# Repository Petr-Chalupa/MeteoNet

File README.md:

# MeteoNet

Simple meteorological net with single root node and multiple sensor nodes.  
Focusing on low power consumption, low data TX and near/far communication.

### FW
> Written in C++  
> No runtime memalloc strategy  
> No unnecessary C++ features

### HW
> Developed in KiCAD  
> Simple design  
> One HW, multiple roles strategy

_For more thorough documentation, please see [docs](/docs)._

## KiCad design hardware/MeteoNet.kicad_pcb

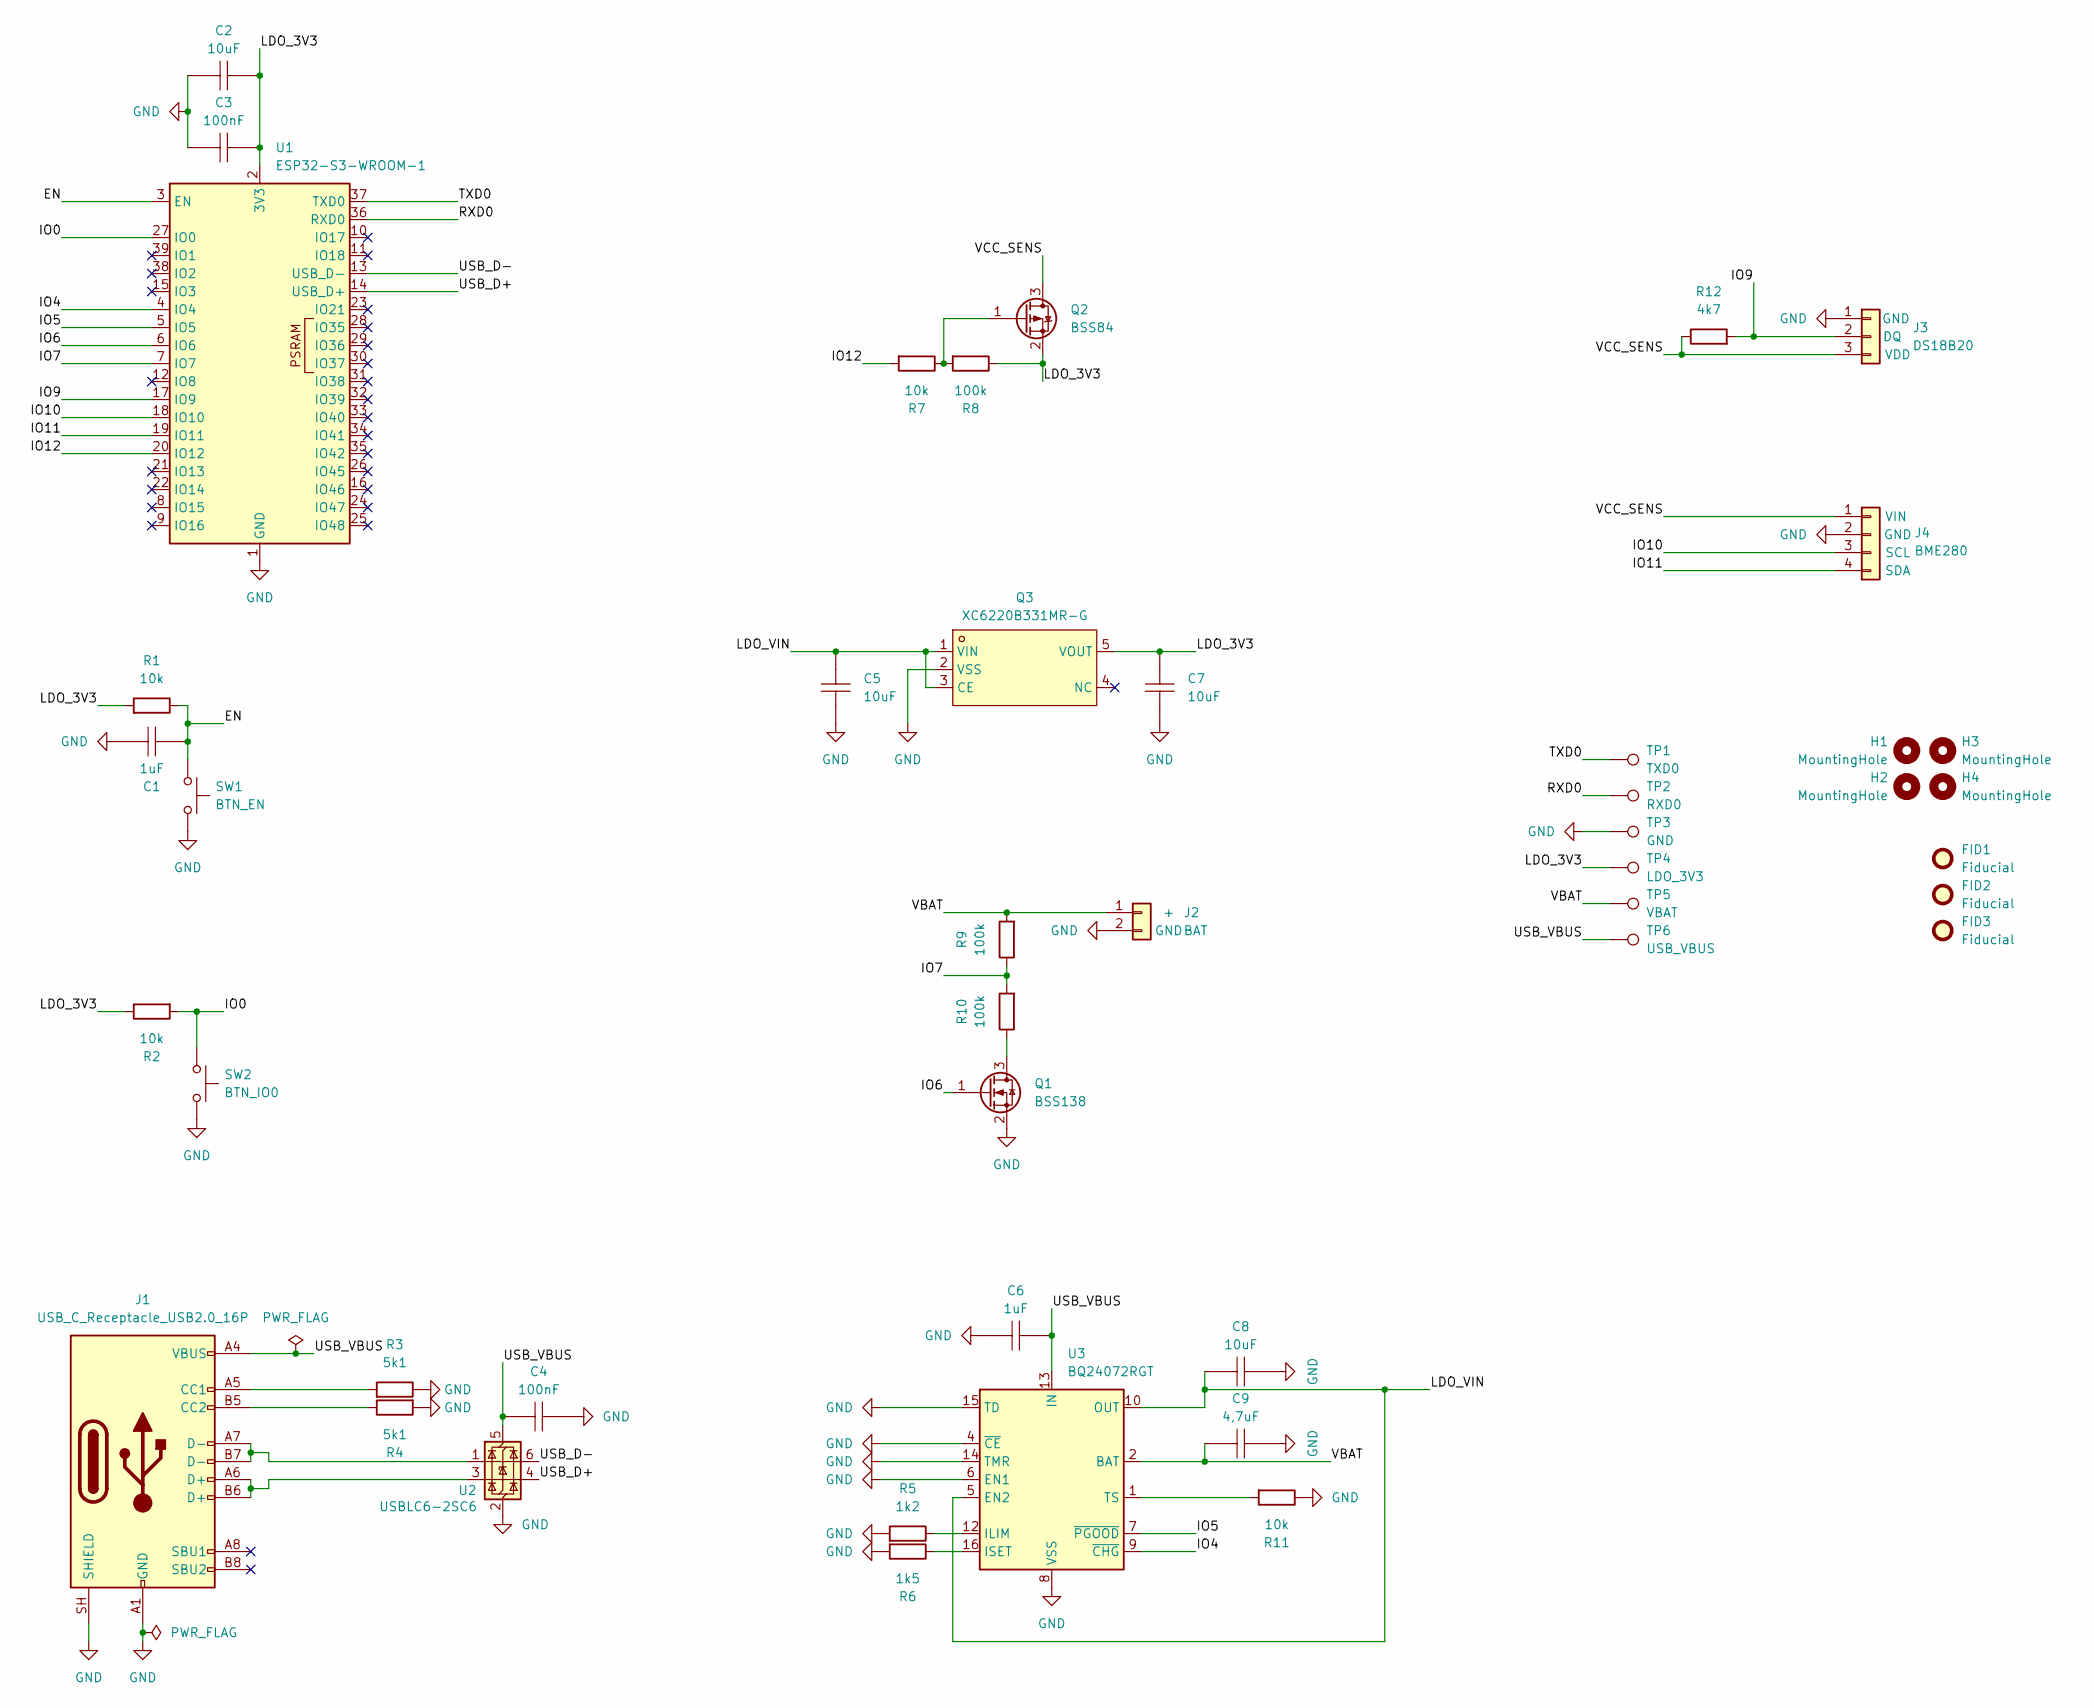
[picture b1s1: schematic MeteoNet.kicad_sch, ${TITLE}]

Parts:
C1: 1uF; C_0603_1608Metric; Voltage Rated 10V; Tolerance ±10%; LCSC Part C19702
C2, C5, C7: 10uF; C_0805_2012Metric; Voltage Rated 10V; Tolerance ±10%; LCSC Part C19702
C3, C4: 100nF; C_0603_1608Metric; Voltage Rated 16V; Tolerance ±10%; LCSC Part C1525
C6: 1uF; C_0603_1608Metric; Voltage Rated 16V; Tolerance ±10%; LCSC Part C1525
C8: 10uF; C_0805_2012Metric; Voltage Rated 16V; Tolerance ±10%; LCSC Part C1525
C9: 4,7uF; C_0805_2012Metric; Voltage Rated 16V; Tolerance ±10%; LCSC Part C1525
FID1, FID2, FID3: Fiducial; Fiducial_1mm_Mask2mm
H1, H2, H3, H4: MountingHole; MountingHole_2.5mm_Pad
J1: USB_C_Receptacle_USB2.0_16P; USB_C_Receptacle_HRO_TYPE-C-31-M-12; LCSC Part # C165948
J2: BAT; JST_PH_B2B-PH-SM4-TB_1x02-1MP_P2.00mm_Vertical; LCSC Part # C160352
J3: DS18B20; PinSocket_1x03_P2.54mm_Vertical_SMD_Pin1Left; LCSC Part # C42379196
J4: BME280; PinSocket_1x04_P2.54mm_Vertical_SMD_Pin1Left; LCSC Part # C42379197
Q1: BSS138; SOT-23; LCSC Part # C52895
Q2: BSS84; SOT-23; LCSC Part # C112238
Q3: XC6220B331MR-G; SOT-23-5; Dropout Voltage 655mV@(1A); Output Voltage 3.3V; LCSC Part C86534
R1, R2, R7, R11: 10k; R_0603_1608Metric; LCSC Part # C25804
R3, R4: 5k1; R_0603_1608Metric; LCSC Part # C23186
R5: 1k2; R_0603_1608Metric; LCSC Part # C22765
R6: 1k5; R_0603_1608Metric; LCSC Part # C22843
R8, R9, R10: 100k; R_0603_1608Metric; LCSC Part # C25803
R12: 4k7; R_0603_1608Metric; LCSC Part # C23162
SW1: BTN_EN; SW_SPST_PTS645Sx43SMTR92; LCSC Part # C2801804
SW2: BTN_IO0; SW_SPST_PTS645Sx43SMTR92; LCSC Part # C2801804
TP1: TXD0; TestPoint_Pad_D1.5mm
TP2: RXD0; TestPoint_Pad_D1.5mm
TP3: GND; TestPoint_Pad_D1.5mm
TP4: LDO_3V3; TestPoint_Pad_D1.5mm
TP5: VBAT; TestPoint_Pad_D1.5mm
TP6: USB_VBUS; TestPoint_Pad_D1.5mm
U1: ESP32-S3-WROOM-1; JLCPCB Part # C2913198
U2: USBLC6-2SC6; SOT-23-6; LCSC Part # C7519
U3: BQ24072RGT; VQFN-16-1EP_3x3mm_P0.5mm_EP1.6x1.6mm; LCSC Part # C140288

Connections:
/EN: C1.2, R1.1, SW1.1, U1.3 (EN)
/IO0: R2.2, SW2.1, U1.27 (IO0)
/IO4: U1.4 (IO4), U3.9 (~CHG)
/IO5: U1.5 (IO5), U3.7 (~PGOOD)
/IO6: Q1.1 (G), U1.6 (IO6)
/IO7: R9.1, R10.2, U1.7 (IO7)
/IO9: J3.2, R12.2, U1.17 (IO9)
/IO10: J4.3, U1.18 (IO10)
/IO11: J4.4, U1.19 (IO11)
/IO12: R7.2, U1.20 (IO12)
/LDO_3V3: C2.2, C3.2, C7.2, Q2.2 (S), Q3.5 (VOUT), R1.2, R2.1, R8.1, TP4.1 (1_1), U1.2 (3V3)
/LDO_VIN: C5.1, C8.2, Q3.1 (VIN), Q3.3 (CE), U3.5 (EN2), U3.10 (OUT), U3.11 (OUT)
/RXD0: TP2.1 (1_1), U1.36 (RXD0)
/TXD0: TP1.1 (1_1), U1.37 (TXD0)
/USB_D+: U1.14 (USB_D+), U2.4 (I/O2)
/USB_D-: U1.13 (USB_D-), U2.6 (I/O1)
/USB_VBUS: C4.1, C6.2, J1.A4 (VBUS), J1.A9 (VBUS), J1.B4 (VBUS), J1.B9 (VBUS), TP6.1 (1_1), U2.5 (VBUS), U3.13 (IN)
/VBAT: C9.1, J2.1, R9.2, TP5.1 (1_1), U3.2 (BAT), U3.3 (BAT)
/VCC_SENS: J3.3, J4.1, Q2.3 (D), R12.1
GND: C1.1, C2.1, C3.1, C4.2, C5.2, C6.1, C7.1, C8.1, C9.2, J1.A1 (GND), J1.A12 (GND), J1.B1 (GND), J1.B12 (GND), J1.SH (SHIELD), J2.2, J3.1, J4.2, Q1.2 (S), Q3.2 (VSS), R3.1, R4.2, R5.2, R6.2, R11.1, SW1.2, SW2.2, TP3.1 (1_1), U1.1 (GND), U1.40 (GND), U1.41 (GND), U2.2 (GND), U3.4 (~CE), U3.6 (EN1), U3.8 (VSS), U3.14 (TMR), U3.15 (TD), U3.17 (VSS)
unnamed: J1.A5 (CC1), R3.2
unnamed: J1.B5 (CC2), R4.1
unnamed: J1.A6 (D+), J1.B6 (D+), U2.3 (I/O2)
unnamed: J1.A7 (D-), J1.B7 (D-), U2.1 (I/O1)
unnamed: Q1.3 (D), R10.1
unnamed: Q2.1 (G), R7.1, R8.2
unnamed: R5.1, U3.12 (ILIM)
unnamed: R6.1, U3.16 (ISET)
unnamed: R11.2, U3.1 (TS)

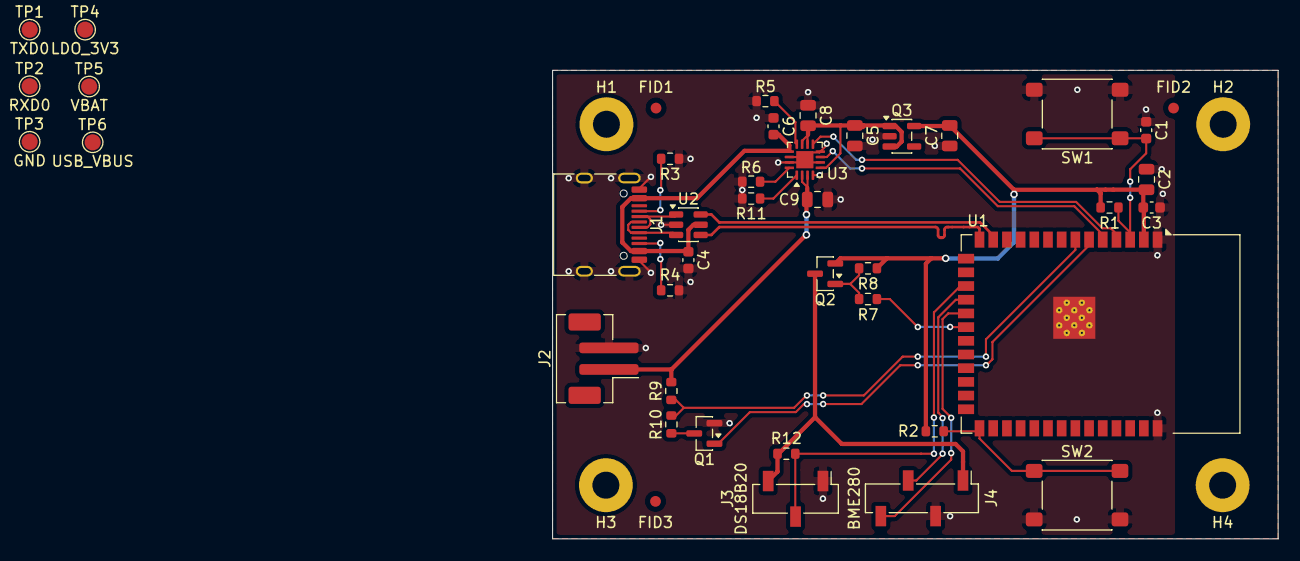
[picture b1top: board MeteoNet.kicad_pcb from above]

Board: 2 copper layers, 67.3 x 43.5 mm, 46 parts (0 on the bottom side), 29 nets.

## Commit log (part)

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2026-03-19 Basic repo structure setup
2026-03-19 Added esp32S3 symbol
2026-03-20 README typo
2026-03-21 Comm headers
2026-03-21 LDO sch.
2026-03-22 Cmake setup fix
2026-03-22 Headers: buffer, lock, sensor
2026-03-22 ESP V3V C
2026-03-22 Stub sensor headers
2026-03-23 Stub sensor deinit
2026-03-23 Buffer fix, frtos mutex added
2026-03-23 Comms initi ret type
2026-03-23 ESPIDF build script
2026-03-23 FRTOS mutex anti-copy pattern
2026-03-27 Restructure, bme280 submodule
2026-03-27 Reworked sensor impl
2026-03-28 WiFi init
